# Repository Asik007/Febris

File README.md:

# Febris
My old Junior year EDD project from 2020 (this was all on zoom)

If your interested in the PCB files and such make an issue and Ill see if I can find them

Hosted at [asik007.github.io/Febris](https://asik007.github.io/Febris)

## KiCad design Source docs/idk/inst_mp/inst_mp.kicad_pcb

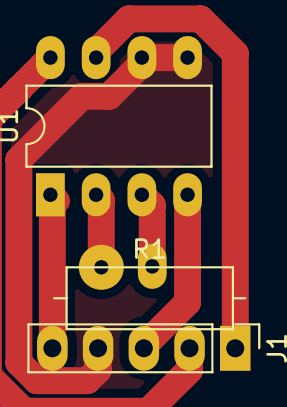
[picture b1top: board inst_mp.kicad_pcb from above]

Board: 2 copper layers, 3 parts (0 on the bottom side), 7 nets.

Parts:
J1: Conn_01x05; PinHeader_1x05_P2.54mm_Vertical
R1: R_Small; R_Axial_DIN0309_L9.0mm_D3.2mm_P12.70mm_Horizontal
U1: AD8422; DIP-8_W7.62mm_LongPads

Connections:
+5V: J1.2, U1.8
GND: J1.4, U1.5, U1.6
unnamed: R1.1, U1.2
unnamed: R1.2, U1.3
Out: J1.1, U1.7
Vin+: J1.3, U1.4
Vin-: J1.5, U1.1

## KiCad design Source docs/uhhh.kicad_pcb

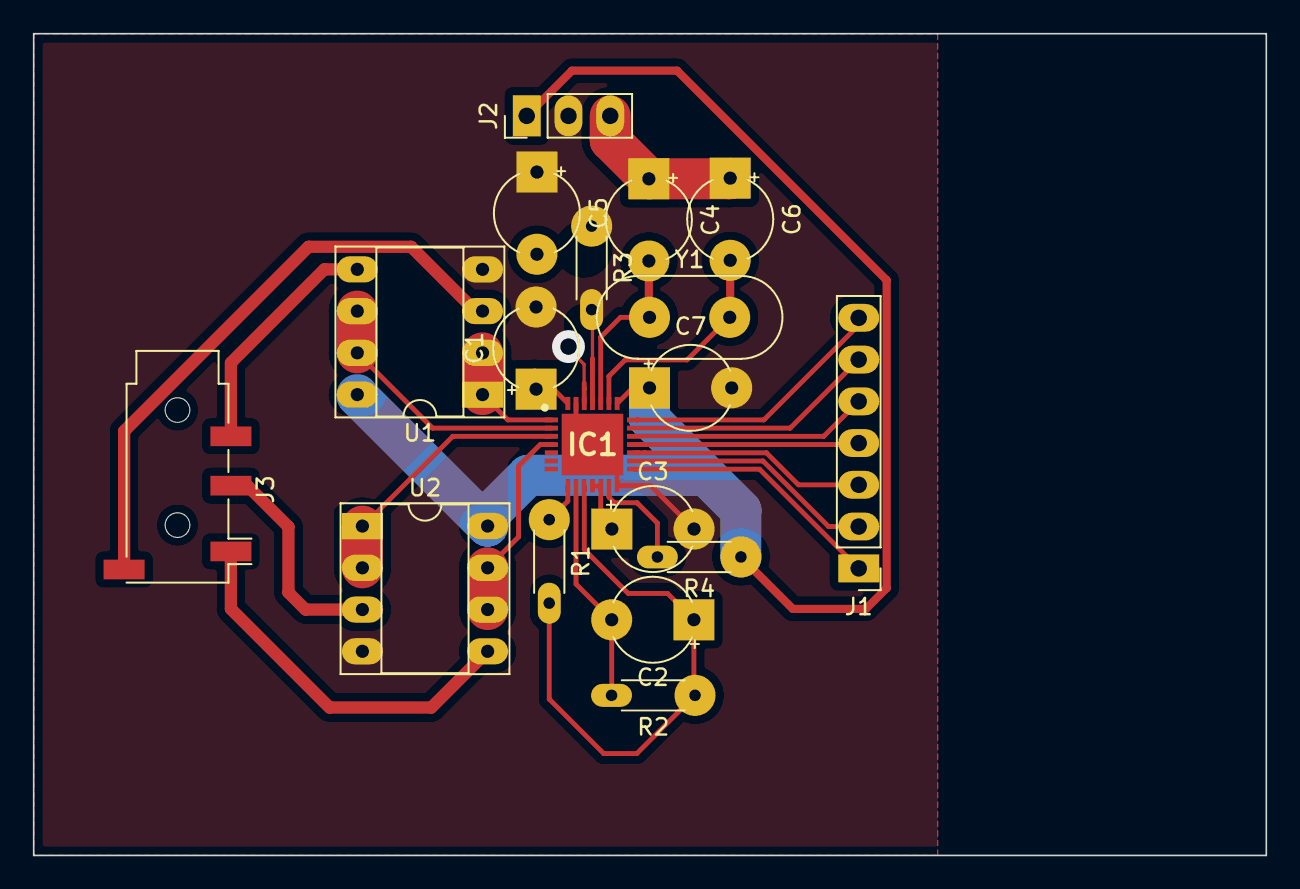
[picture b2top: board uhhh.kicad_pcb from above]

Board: 2 copper layers, 75.0 x 50.0 mm, 18 parts (0 on the bottom side), 28 nets.

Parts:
C1, C7: .1u; tht_cap
C2: C1 in DS; tht_cap
C3: .1 u; tht_cap
C4, C6: 22pf; tht_cap
C5: 1u; tht_cap
IC1: ADS1293CISQ_NOPB; QFN50P500X500X80-29N
J1: Conn_01x07; PinHeader_1x07_P2.54mm_Vertical
J2: Conn_01x03; header_3
J3: AudioJack4; Jack_3.5mm_PJ320D_Horizontal
R1: R1 in DS; R_Axial_DIN0204_L3.6mm_D1.6mm_P5.08mm_Horizontal
R2: R2 in DS; R_Axial_DIN0204_L3.6mm_D1.6mm_P5.08mm_Horizontal
R3, R4: 1M; R_Axial_DIN0204_L3.6mm_D1.6mm_P5.08mm_Horizontal
U1, U2: LM358; dip_8
Y1: 4.096 Mhz; Crystal_HC49-U_Vertical

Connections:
+3V3: C7.1, IC1.22, J2.1, R3.1, R4.1, U1.8, U2.8
+5V: C1.1, C4.1, C6.1, IC1.28, J2.3
ALARMB: IC1.15, J1.1
CLK: IC1.21, J1.7
CSB: IC1.16, J1.2
DRDYB: IC1.20, J1.6
GND: U1.4, U2.4
GND1: C1.2, C3.2, C5.1, C7.2, IC1.14, IC1.27, IC1.29, J2.2
LA_ECG: J3.R2, U1.5
LL_ECG: J3.T, U2.5
unnamed: C2.1, IC1.10, R1.2, R2.1
unnamed: C2.2, IC1.9, R2.2
unnamed: C3.1, IC1.11, IC1.12
unnamed: C4.2, IC1.24, Y1.1
unnamed: C5.2, IC1.26
unnamed: C6.2, IC1.23, Y1.2
unnamed: IC1.1, U1.1, U1.2
unnamed: IC1.2, U1.6, U1.7
unnamed: IC1.3, U2.1, U2.2
unnamed: IC1.4, U2.6, U2.7
unnamed: IC1.8, R1.1
unnamed: IC1.13, R4.2
unnamed: IC1.25, R3.2
RA_ECG: J3.S, U1.3
RL_ECG: J3.R1, U2.3
SCLK: IC1.17, J1.3
SDI: IC1.18, J1.4
SDO: IC1.19, J1.5

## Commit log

2022-08-23 upload everything
2022-08-23 edit
2023-03-07 found it
2025-05-26 upload all the project files
2025-05-26 National Instruments FPGA Board file for MultiSIM (DEFB.ucf)
